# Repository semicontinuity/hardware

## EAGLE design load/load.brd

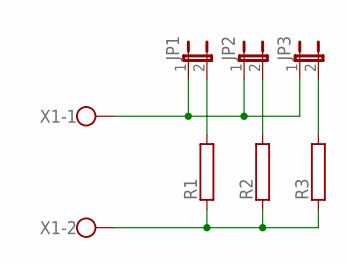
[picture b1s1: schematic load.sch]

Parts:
JP1, JP2, JP3: JP1E; JP1
R1, R2, R3: RRWM8X26; RWM8X26
X1: W237-02P; W237-132

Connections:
GND: R1.1, R2.1, R3.1, X1.2
unnamed: JP1.2, R1.2
unnamed: JP2.2, R2.2
unnamed: JP3.2, R3.2
VCC: JP1.1, JP2.1, JP3.1, X1.1

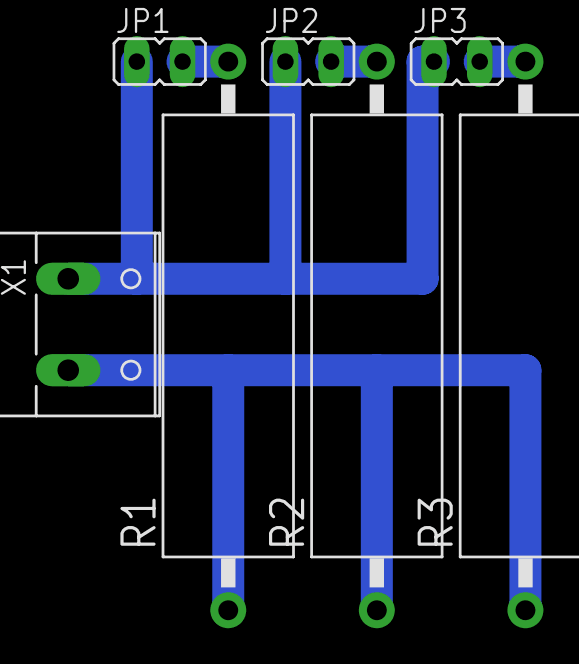
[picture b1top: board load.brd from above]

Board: 2 copper layers, 7 parts (0 on the bottom side), 5 nets.

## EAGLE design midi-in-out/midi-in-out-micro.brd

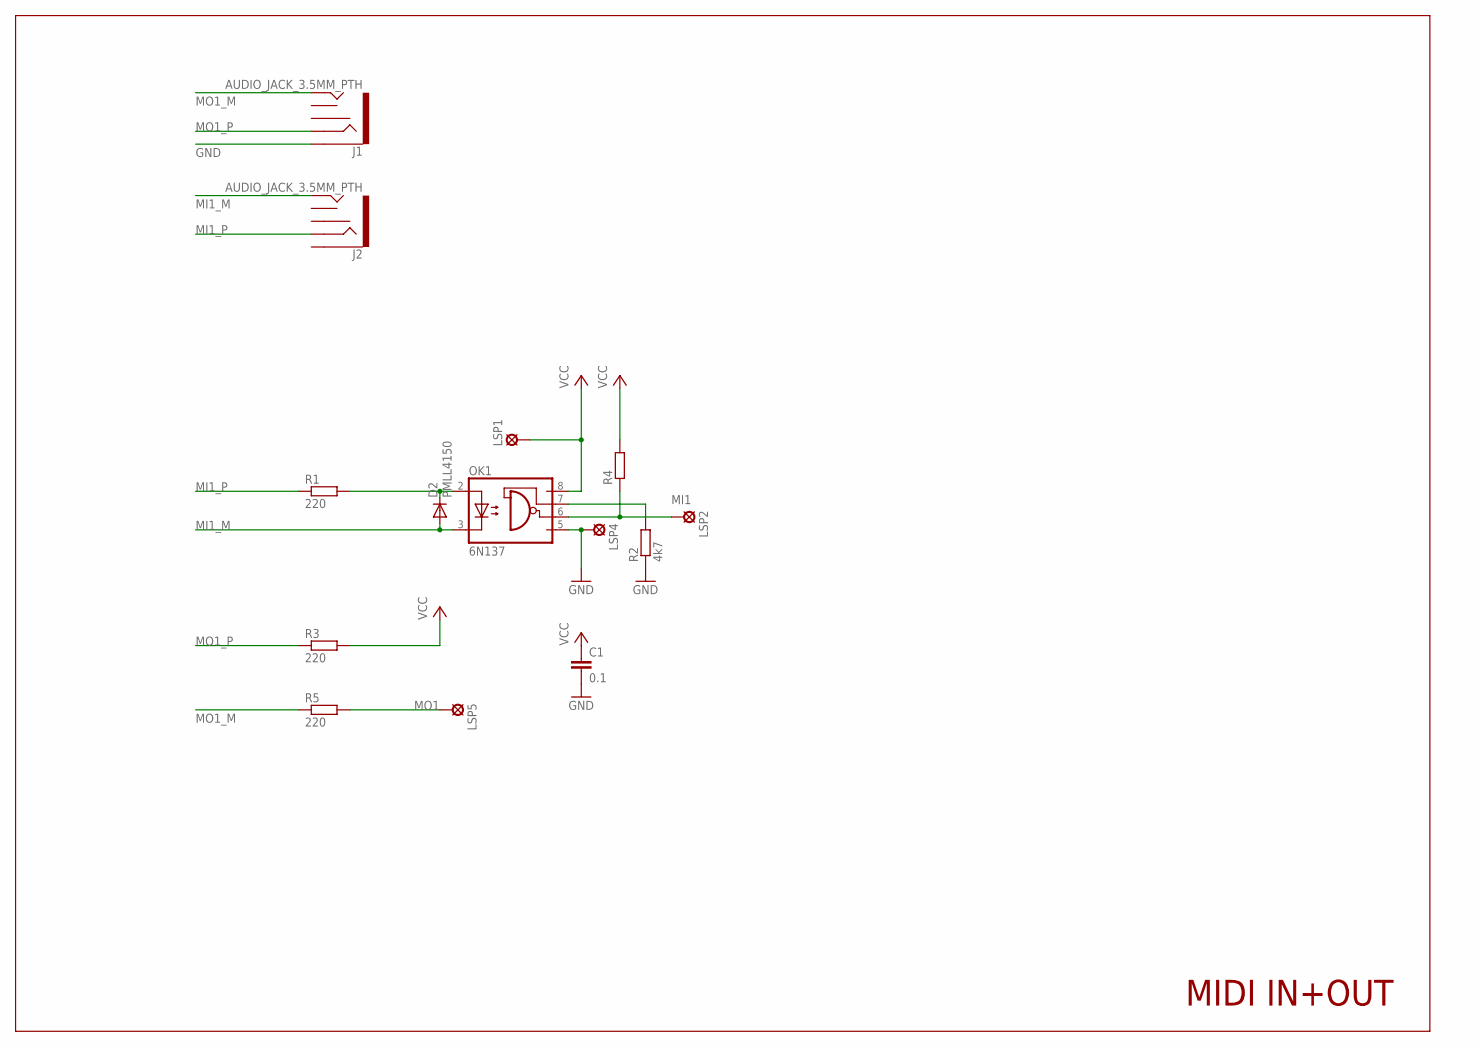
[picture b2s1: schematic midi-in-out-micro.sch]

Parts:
C1: 0.1; C0805
D2: PMLL4150; SOD80C
J1, J2: AUDIO_JACK_3.5MM_PTH; AUDIO-JACK
LSP1, LSP2, LSP4, LSP5: MCS10B
OK1: 6N137; DIL08
R1, R3, R5: 220; R0805
R2: 4k7; R0805
R4: R-EU_0207/5V; 0207/5V

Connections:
GND: C1.2, J1.SLEEVE, LSP4.MP, OK1.5 (GND), R2.1
MI1: LSP2.MP, OK1.6 (VO), R4.1
MI1_M: D2.A, J2.TIP, OK1.3 (C)
MI1_P: J2.RING, R1.1
MO1: LSP5.MP, R5.2
MO1_M: J1.TIP, R5.1
MO1_P: J1.RING, R3.1
unnamed: D2.C, OK1.2 (A), R1.2
unnamed: OK1.7 (VE), R2.2
VCC: C1.1, LSP1.MP, OK1.8 (VCC), R3.2, R4.2

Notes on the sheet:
MIDI IN+OUT

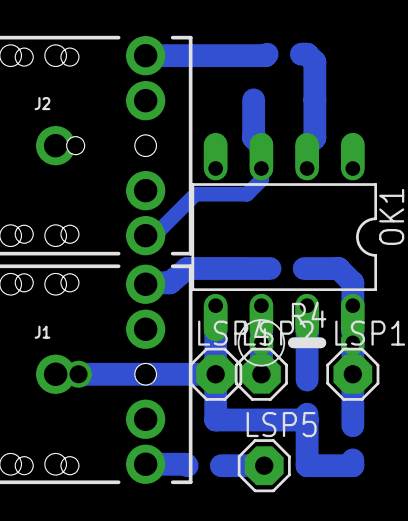
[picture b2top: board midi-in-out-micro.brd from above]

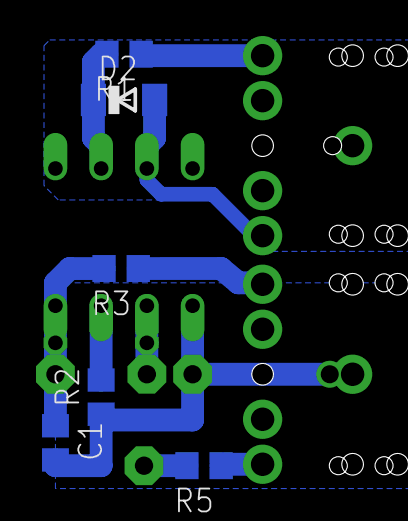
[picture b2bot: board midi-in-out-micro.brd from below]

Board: 2 copper layers, 14 parts (6 on the bottom side), 10 nets.

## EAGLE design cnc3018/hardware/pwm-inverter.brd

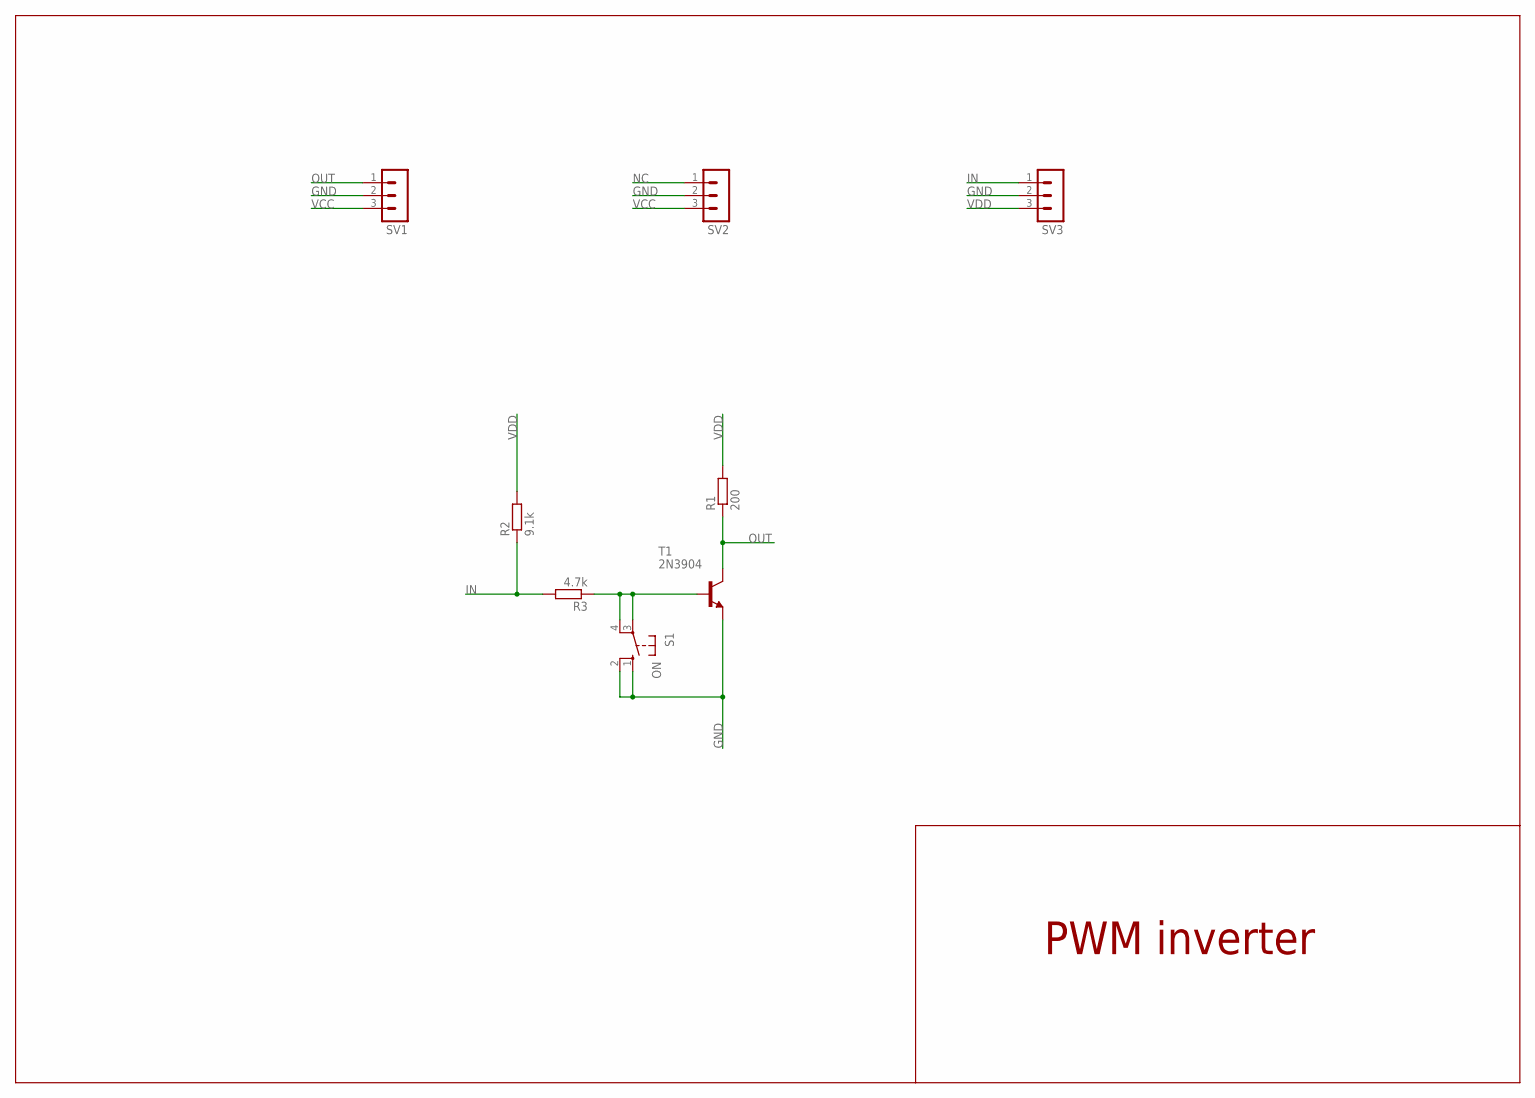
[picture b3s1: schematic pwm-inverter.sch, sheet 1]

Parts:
R1: 200; 0207/10
R2: 9.1k; 0207/10
R3: 4.7k; 0207/10
S1: ON; B3F-10XX
SV1, SV2, SV3: MA03-1
T1: 2N3904; TO92

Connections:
GND: S1.1 (S), S1.2 (S1), SV1.2, SV2.2, SV3.2, T1.3 (E)
IN: R2.1, R3.2, SV3.1
unnamed: R3.1, S1.3, S1.4 (P1), T1.2 (B)
NC: SV2.1
OUT: R1.1, SV1.1, T1.1 (C)
VCC: SV1.3, SV2.3
VDD: R1.2, R2.2, SV3.3

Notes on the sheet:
PWM inverter

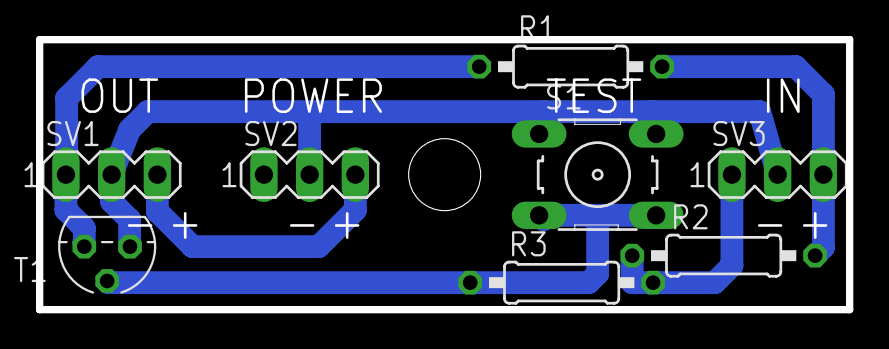
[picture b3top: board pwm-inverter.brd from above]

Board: 2 copper layers, 45.0 x 15.0 mm, 8 parts (0 on the bottom side), 6 nets.

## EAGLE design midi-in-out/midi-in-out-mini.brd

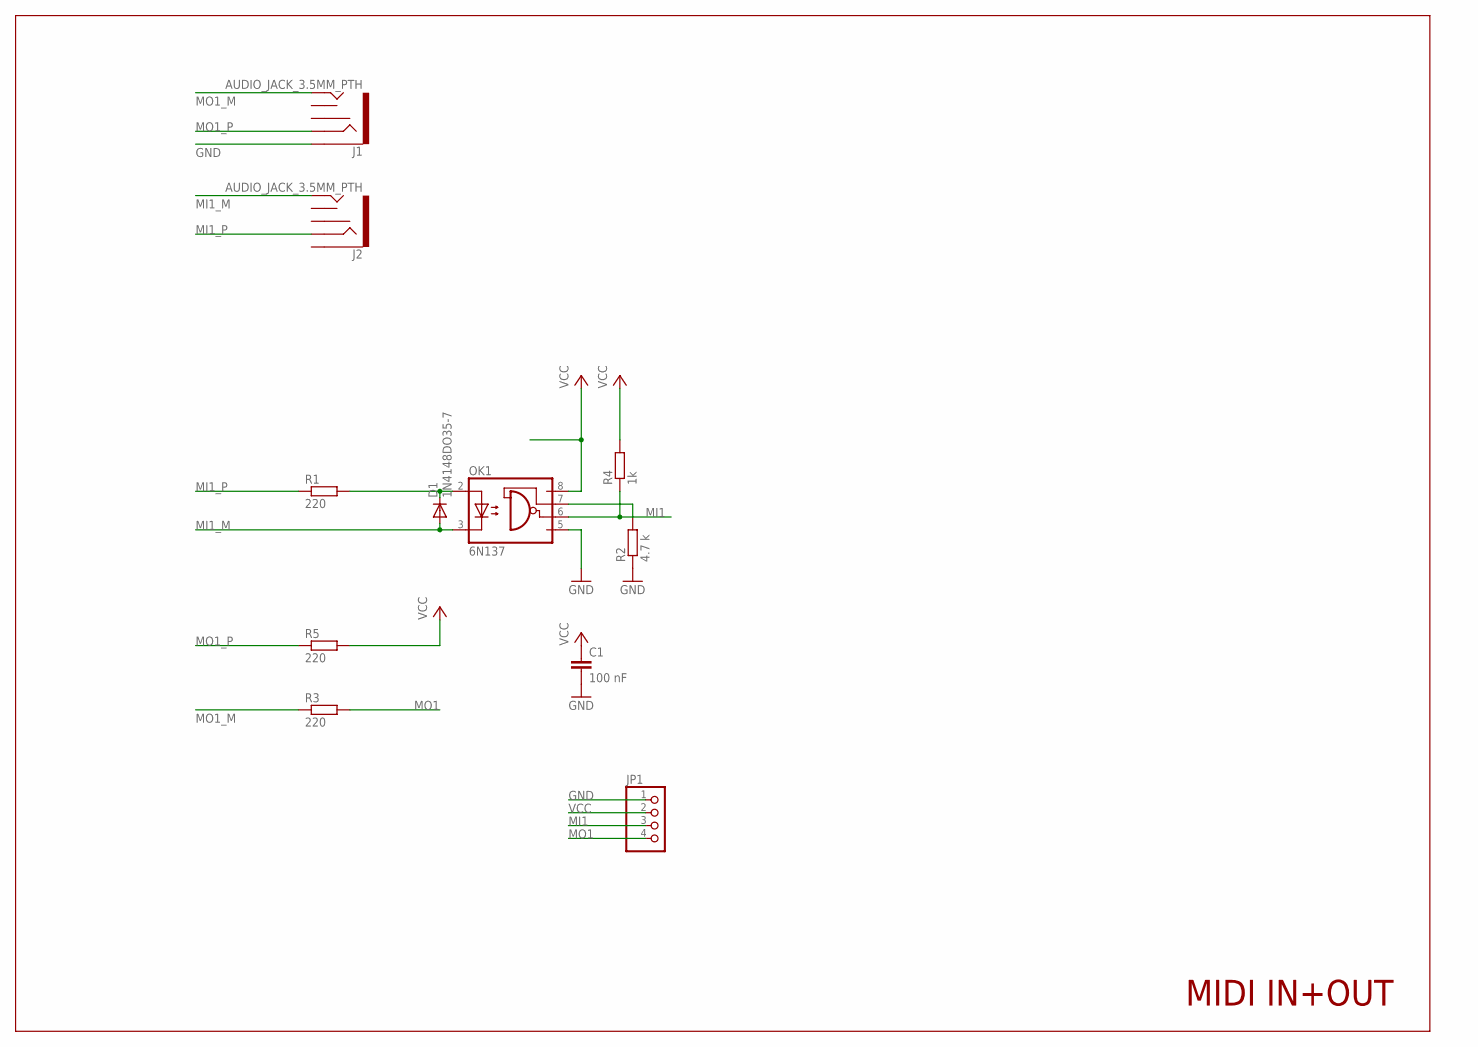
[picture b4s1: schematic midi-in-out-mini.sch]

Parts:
C1: 100 nF; C025-024X044
D1: 1N4148DO35-7; DO35-7
J1, J2: AUDIO_JACK_3.5MM_PTH; AUDIO-JACK
JP1: PINHD-1X4/90; 1X04/90
OK1: 6N137; DIL08
R1, R3, R5: 220; 0204/7
R2: 4.7 k; 0204/7
R4: 1k; 0204/7

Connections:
GND: C1.2, J1.SLEEVE, JP1.1, OK1.5 (GND), R2.1
MI1: JP1.3, OK1.6 (VO), R4.1
MI1_M: D1.A, J2.TIP, OK1.3 (C)
MI1_P: J2.RING, R1.1
MO1: JP1.4, R3.2
MO1_M: J1.TIP, R3.1
MO1_P: J1.RING, R5.1
unnamed: D1.C, OK1.2 (A), R1.2
unnamed: OK1.7 (VE), R2.2
VCC: C1.1, JP1.2, OK1.8 (VCC), R4.2, R5.2

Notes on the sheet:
MIDI IN+OUT

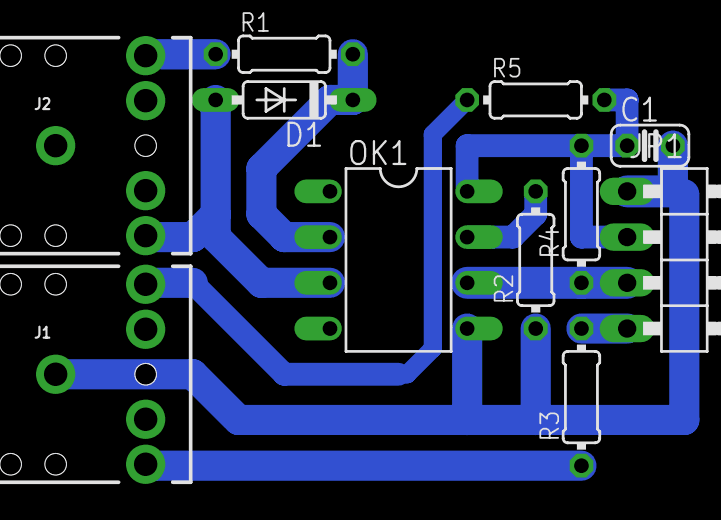
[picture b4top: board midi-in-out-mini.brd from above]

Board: 2 copper layers, 11 parts (0 on the bottom side), 10 nets.

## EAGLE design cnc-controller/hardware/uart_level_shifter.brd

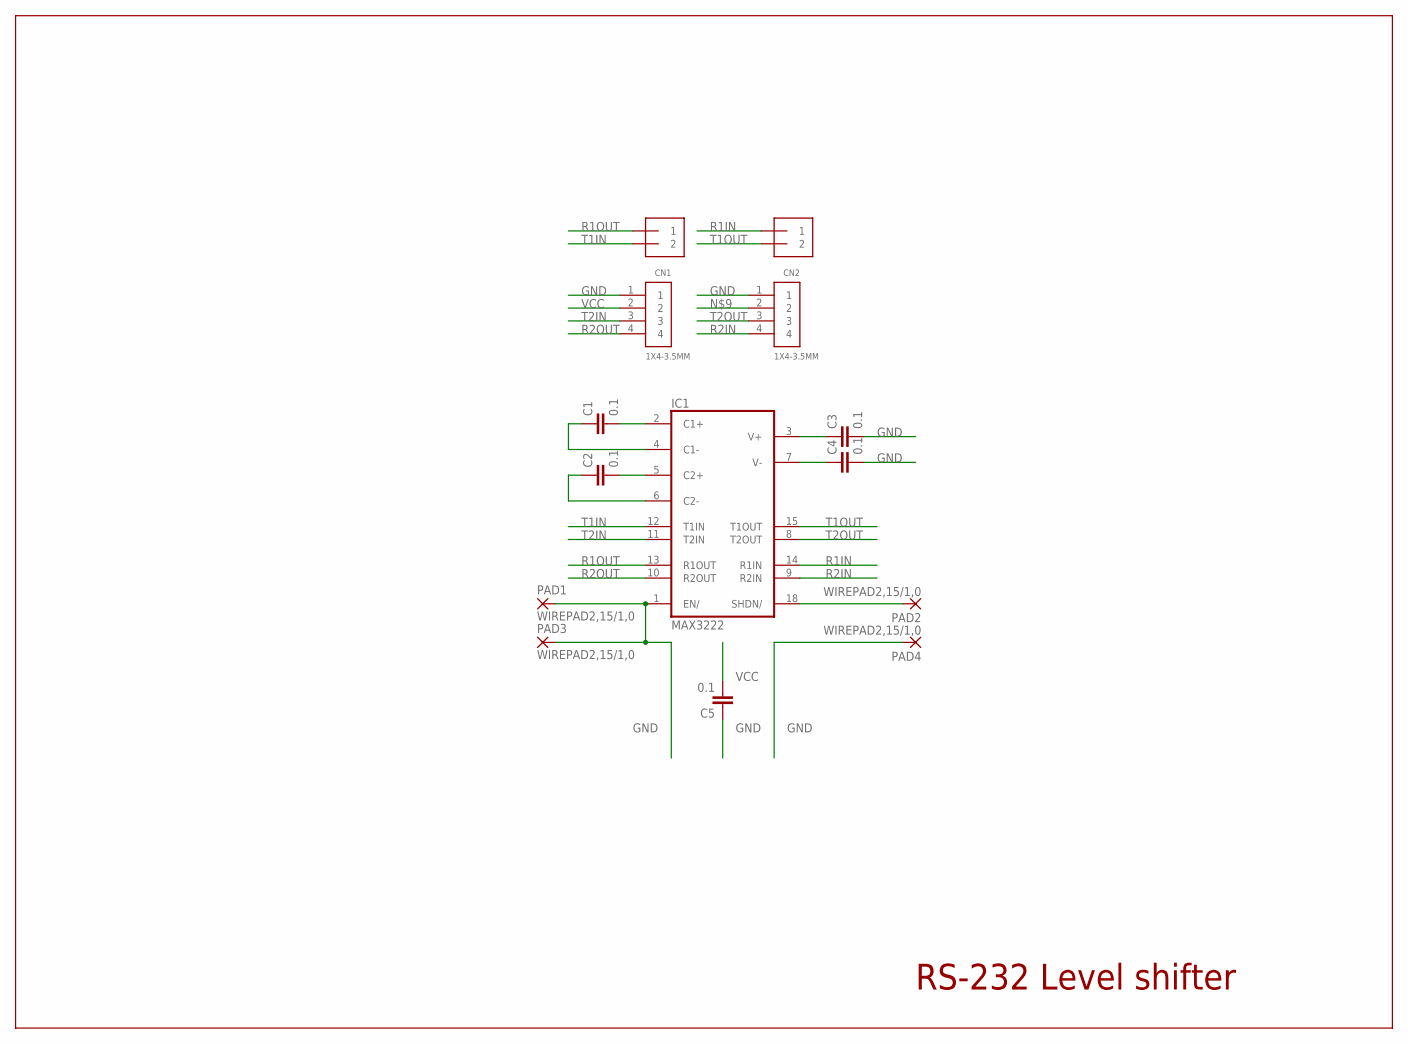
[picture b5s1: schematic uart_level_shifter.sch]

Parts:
C1, C2, C3, C4, C5: 0.1; C0805
CN1, CN2: 1X4-3.5MM; 1X04-3.5MM
IC1: MAX3222; DIL18
J1, J2: 1X2-3.5MM
PAD1, PAD2, PAD3, PAD4: WIREPAD2,15/1,0; 2,15/1,0

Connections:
GND: C3.2, C4.2, C5.1, CN1.1, CN2.1, IC1.1 (EN/), IC1.16 (GND), PAD1.1, PAD3.1, PAD4.1
unnamed: C2.2, IC1.5 (C2+)
unnamed: C2.1, IC1.6 (C2-)
unnamed: C1.1, IC1.4 (C1-)
unnamed: C1.2, IC1.2 (C1+)
unnamed: C3.1, IC1.3 (V+)
unnamed: IC1.18 (SHDN/), PAD2.1
unnamed: C4.1, IC1.7 (V-)
R1IN: IC1.14 (R1IN), J2.1
R1OUT: IC1.13 (R1OUT), J1.1
R2IN: CN2.4, IC1.9 (R2IN)
R2OUT: CN1.4, IC1.10 (R2OUT)
T1IN: IC1.12 (T1IN), J1.2
T1OUT: IC1.15 (T1OUT), J2.2
T2IN: CN1.3, IC1.11 (T2IN)
T2OUT: CN2.3, IC1.8 (T2OUT)
VCC: C5.2, CN1.2, IC1.17 (VCC)

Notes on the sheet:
RS-232 Level shifter

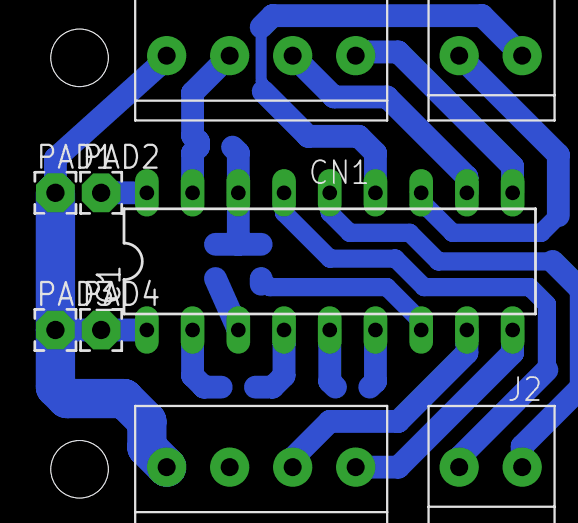
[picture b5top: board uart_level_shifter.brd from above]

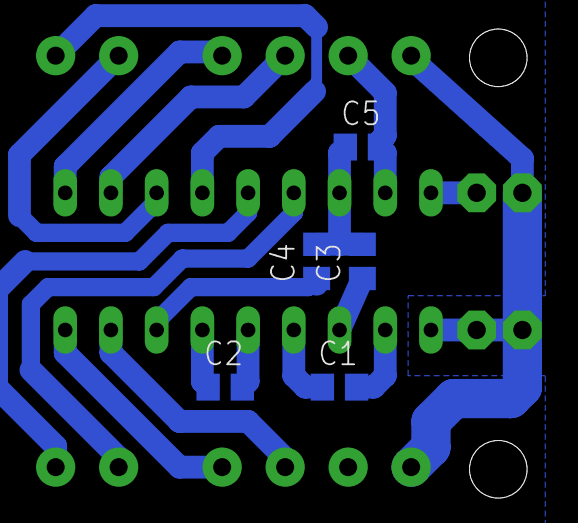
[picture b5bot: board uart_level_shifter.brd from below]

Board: 2 copper layers, 14 parts (5 on the bottom side), 17 nets.

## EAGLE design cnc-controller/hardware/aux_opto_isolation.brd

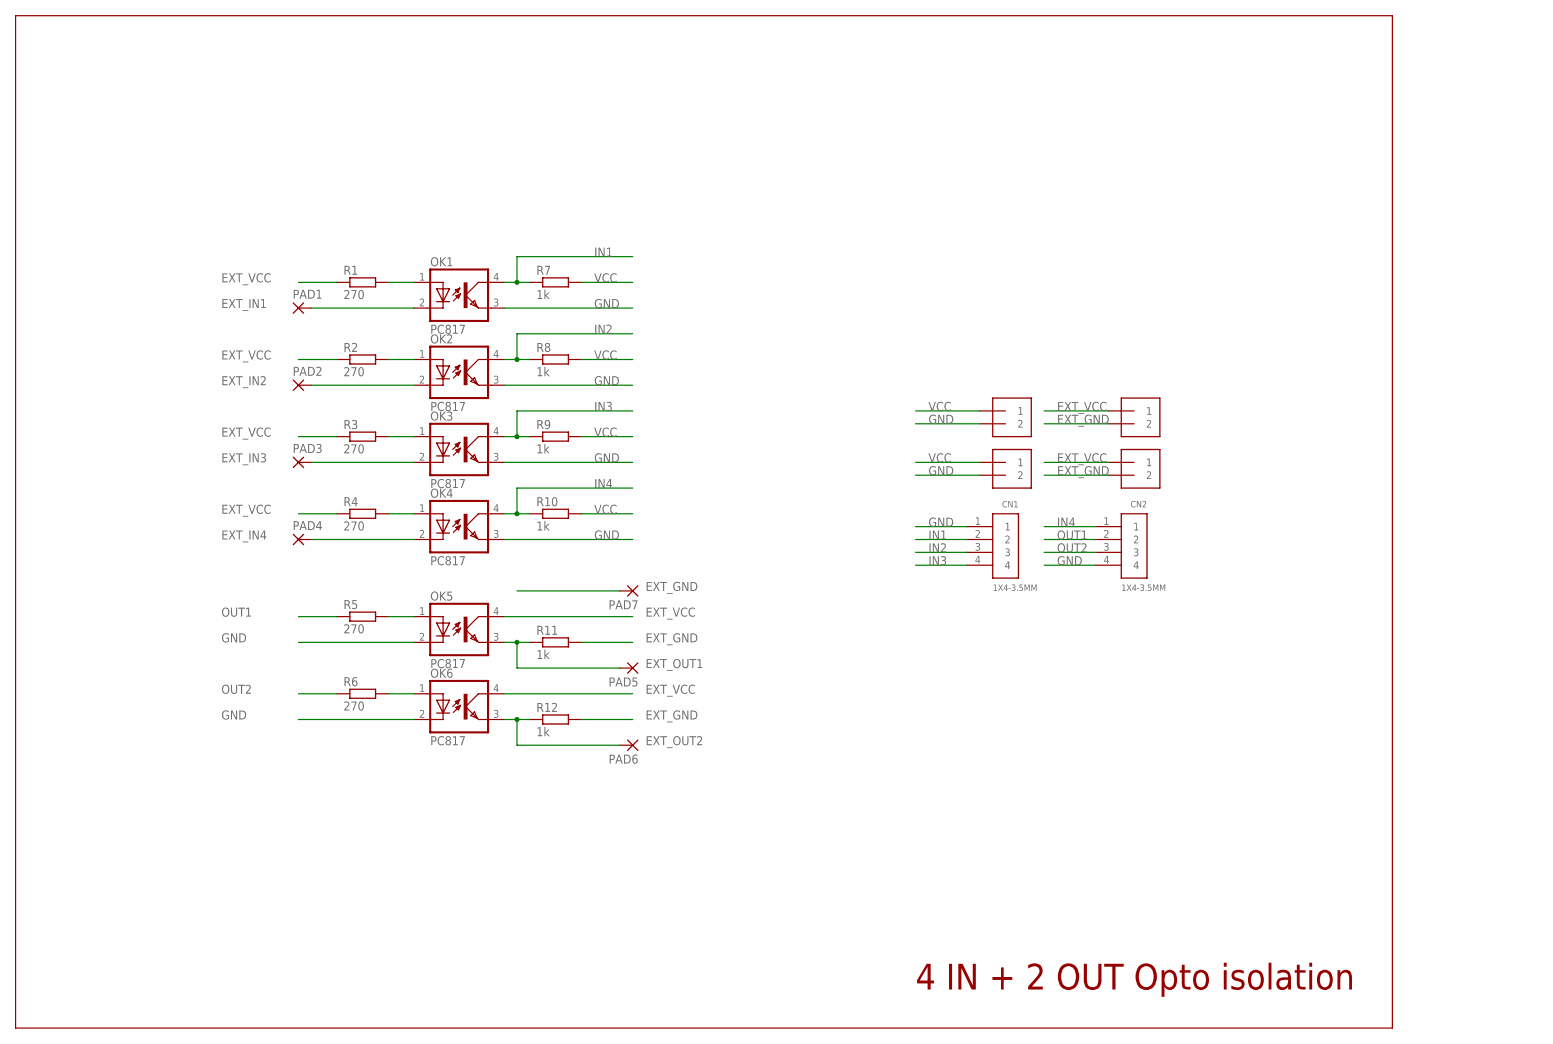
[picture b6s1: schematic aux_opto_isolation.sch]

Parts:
CN1, CN2: 1X4-3.5MM; 1X04-3.5MM
J1, J2, J3, J4: 1X2-3.5MM
OK1, OK2, OK3, OK4, OK5, OK6: PC817; DIL04
PAD1, PAD2, PAD3, PAD4, PAD5, PAD6, PAD7: 2,54/1,0
R1, R2, R3, R4, R5, R6: 270; M0805
R7, R8, R9, R10, R11, R12: 1k; M0805

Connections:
EXT_GND: J2.2, J4.2, PAD7.1, R11.2, R12.2
EXT_IN1: OK1.2 (C), PAD1.1
EXT_IN2: OK2.2 (C), PAD2.1
EXT_IN3: OK3.2 (C), PAD3.1
EXT_IN4: OK4.2 (C), PAD4.1
EXT_OUT1: OK5.3 (EMIT), PAD5.1, R11.1
EXT_OUT2: OK6.3 (EMIT), PAD6.1, R12.1
EXT_VCC: J2.1, J4.1, OK5.4 (COL), OK6.4 (COL), R1.1, R2.1, R3.1, R4.1
GND: CN1.1, CN2.4, J1.2, J3.2, OK1.3 (EMIT), OK2.3 (EMIT), OK3.3 (EMIT), OK4.3 (EMIT), OK5.2 (C), OK6.2 (C)
IN1: CN1.2, OK1.4 (COL), R7.1
IN2: CN1.3, OK2.4 (COL), R8.1
IN3: CN1.4, OK3.4 (COL), R9.1
IN4: CN2.1, OK4.4 (COL), R10.1
unnamed: OK5.1 (A), R5.2
unnamed: OK6.1 (A), R6.2
unnamed: OK2.1 (A), R2.2
unnamed: OK3.1 (A), R3.2
unnamed: OK4.1 (A), R4.2
unnamed: OK1.1 (A), R1.2
OUT1: CN2.2, R5.1
OUT2: CN2.3, R6.1
VCC: J1.1, J3.1, R7.2, R8.2, R9.2, R10.2

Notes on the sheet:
4 IN + 2 OUT Opto isolation

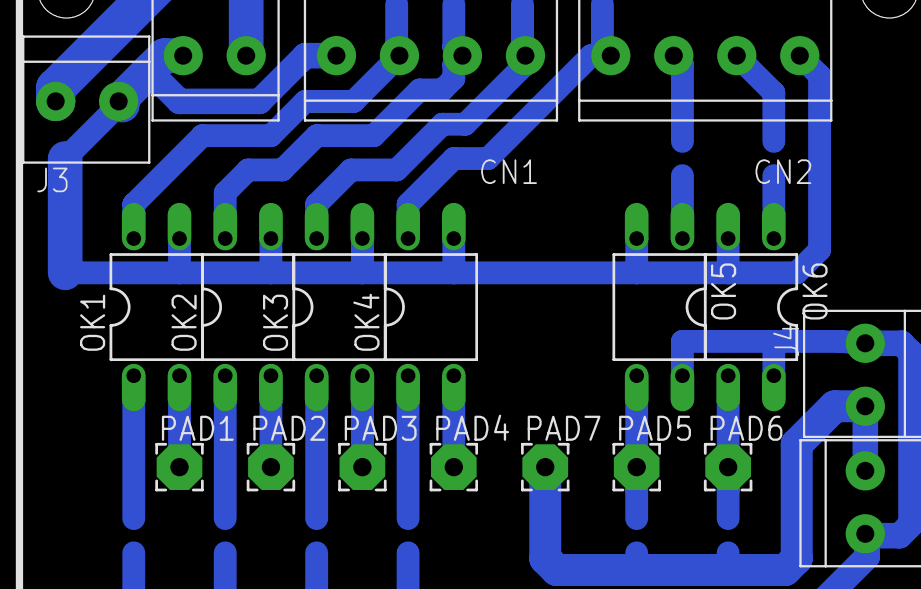
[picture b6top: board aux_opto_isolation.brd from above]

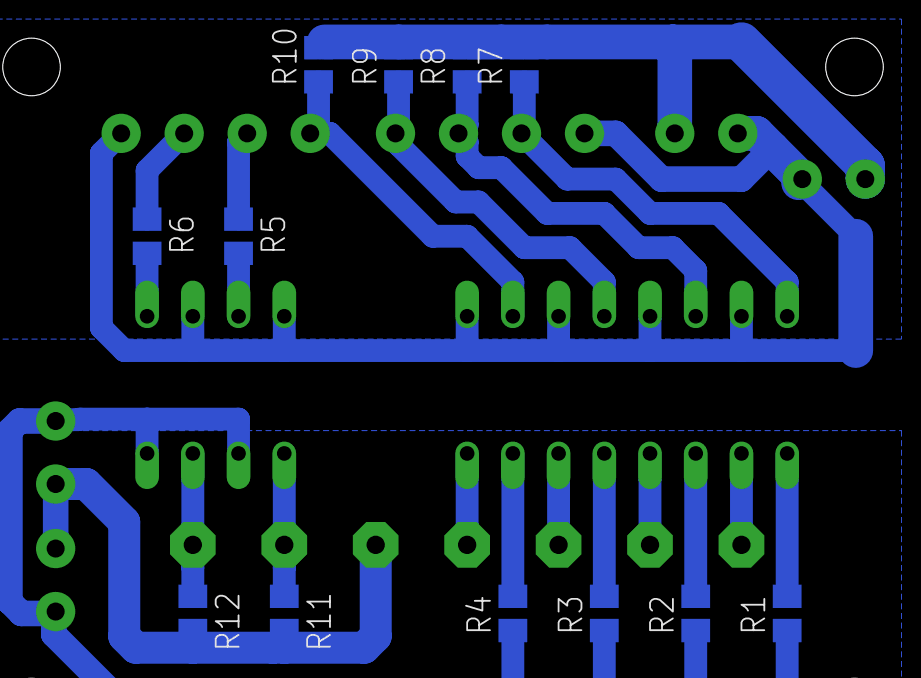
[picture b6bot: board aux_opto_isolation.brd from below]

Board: 2 copper layers, 31 parts (12 on the bottom side), 22 nets.

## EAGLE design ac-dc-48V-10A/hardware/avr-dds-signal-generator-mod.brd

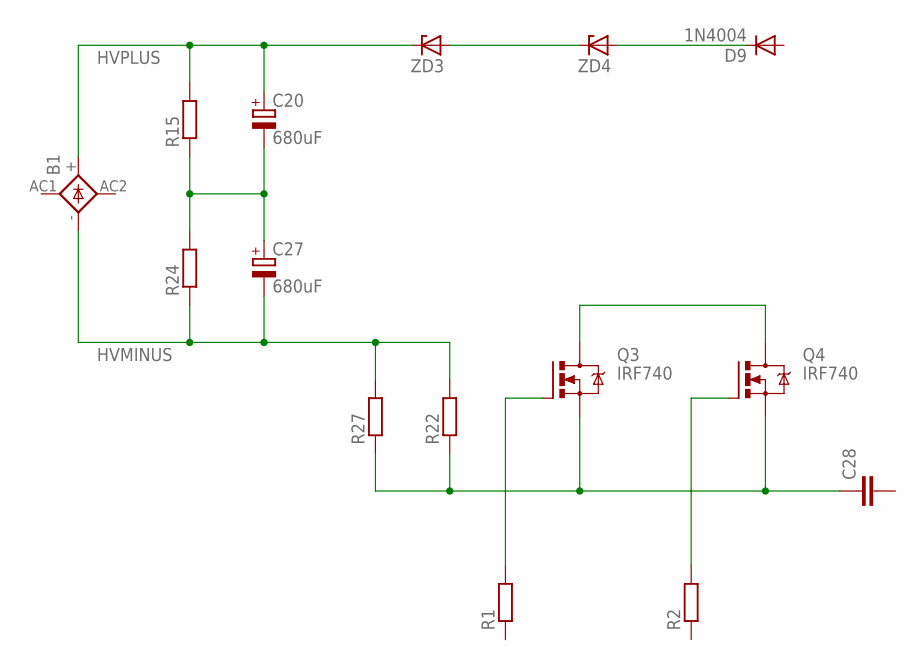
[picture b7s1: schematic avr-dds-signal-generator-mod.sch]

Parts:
B1: KBU
C20, C27: 680uF; EB22,5D
C28: C-EU025-025X050; C025-025X050
D9: 1N4004; DO41-10
Q3, Q4: IRF740; TO220BV
R1, R2, R15, R24: R-EU_0309/12; 0309/12
R22, R27: R-EU_0414/15; 0414/15
ZD3, ZD4: ZENER-DIODEC1702-15; C1702-15

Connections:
HVMINUS: B1.-, C27.-, R22.2, R24.1, R27.2
HVPLUS: B1.+, C20.+, R15.2, ZD3.C
unnamed: ZD3.A, ZD4.C
unnamed: C20.-, C27.+, R15.1, R24.2
unnamed: D9.C, ZD4.A
unnamed: C28.1, Q3.S, Q4.S, R22.1, R27.1
unnamed: Q3.D, Q4.D
unnamed: Q3.G, R1.2
unnamed: Q4.G, R2.2

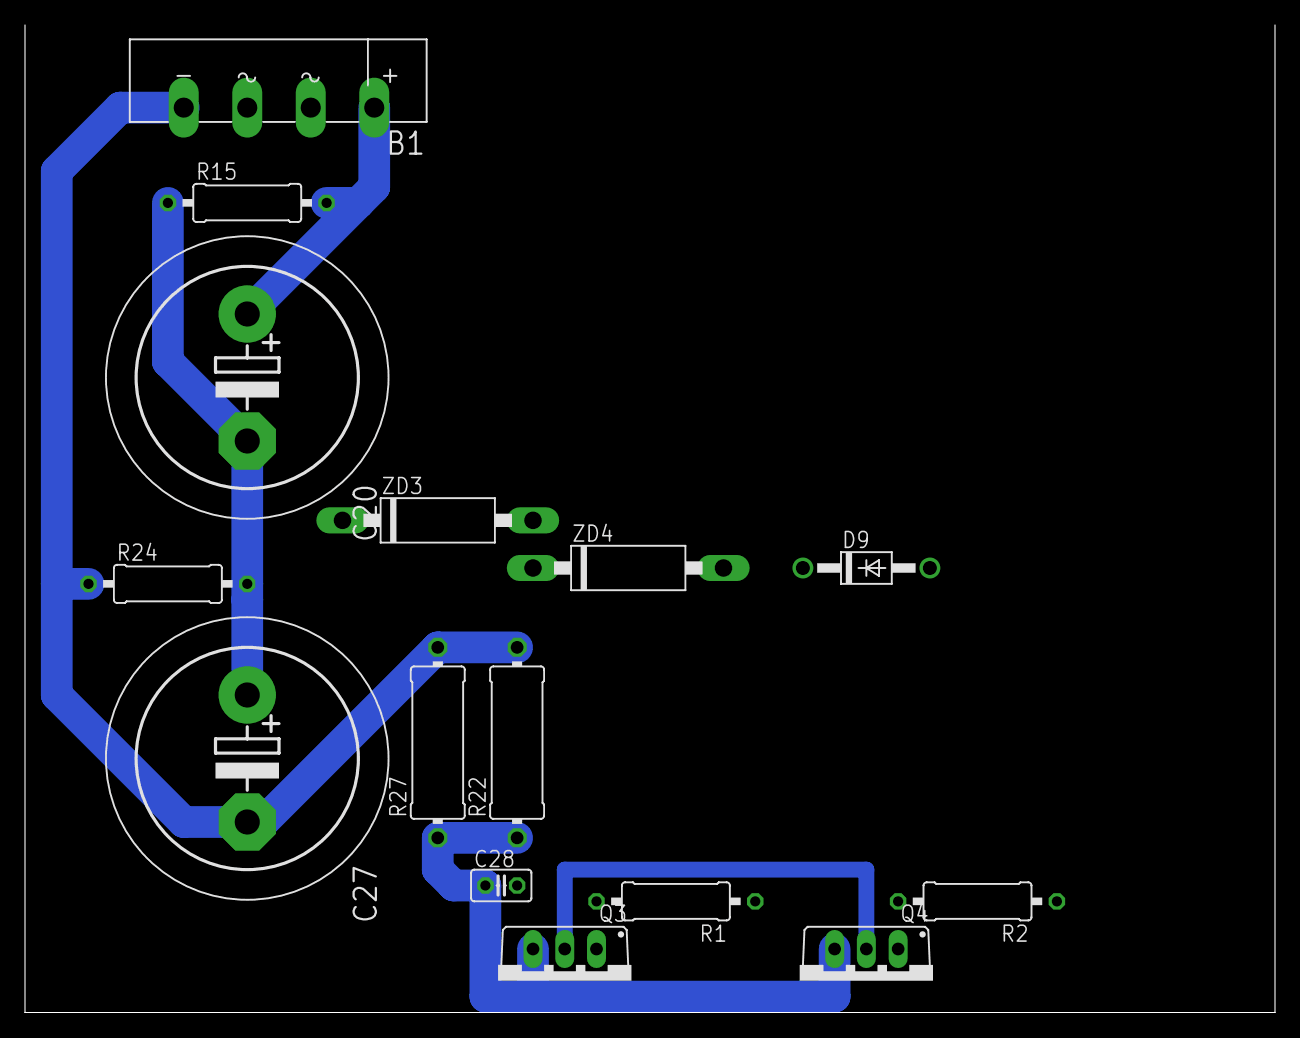
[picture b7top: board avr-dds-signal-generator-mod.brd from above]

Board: 2 copper layers, 100.0 x 79.0 mm, 15 parts (0 on the bottom side), 9 nets.

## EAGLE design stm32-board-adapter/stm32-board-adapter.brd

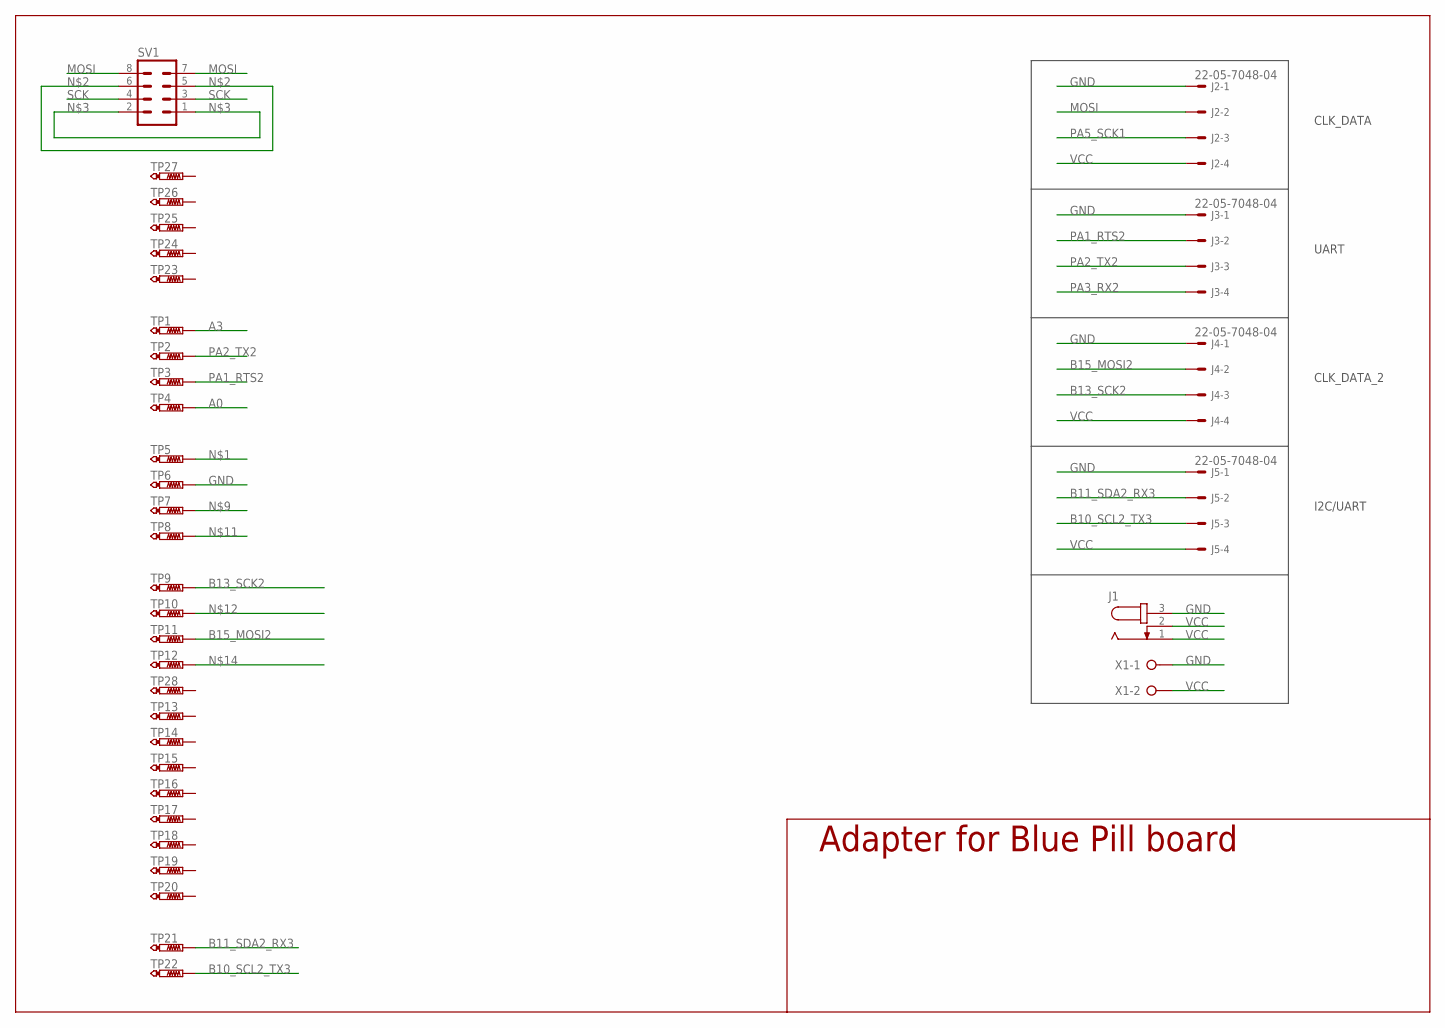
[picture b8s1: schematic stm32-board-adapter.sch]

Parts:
J1: JACK-PLUG1; SPC4078
J2, J3, J4, J5: 22-05-7048-04; 7395-04
SV1: MA04-2
TP1, TP2, TP3, TP4, TP5, TP6, TP7, TP8, TP9, TP10, TP11, TP12, TP13, TP14, TP15, TP16, TP17, TP18, TP19, TP20, TP21, TP22, TP23, TP24, TP25, TP26, TP27, TP28: PTR1PAD1-13; P1-13
X1: W237-02P; W237-132

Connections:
A0: TP4.TP
A3: TP1.TP
B10_SCL2_TX3: J5.3, TP22.TP
B11_SDA2_RX3: J5.2, TP21.TP
B13_SCK2: J4.3, TP9.TP
B15_MOSI2: J4.2, TP11.TP
GND: J1.3, J2.1, J3.1, J4.1, J5.1, TP6.TP, X1.1
MOSI: J2.2, SV1.7, SV1.8
unnamed: SV1.5, SV1.6
unnamed: SV1.1, SV1.2
PA1_RTS2: J3.2, TP3.TP
PA2_TX2: J3.3, TP2.TP
PA3_RX2: J3.4
PA5_SCK1: J2.3
SCK: SV1.3, SV1.4
VCC: J1.1, J1.2, J2.4, J4.4, J5.4, X1.2

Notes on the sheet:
Adapter for Blue Pill board
I2C/UART
CLK_DATA
UART
CLK_DATA_2

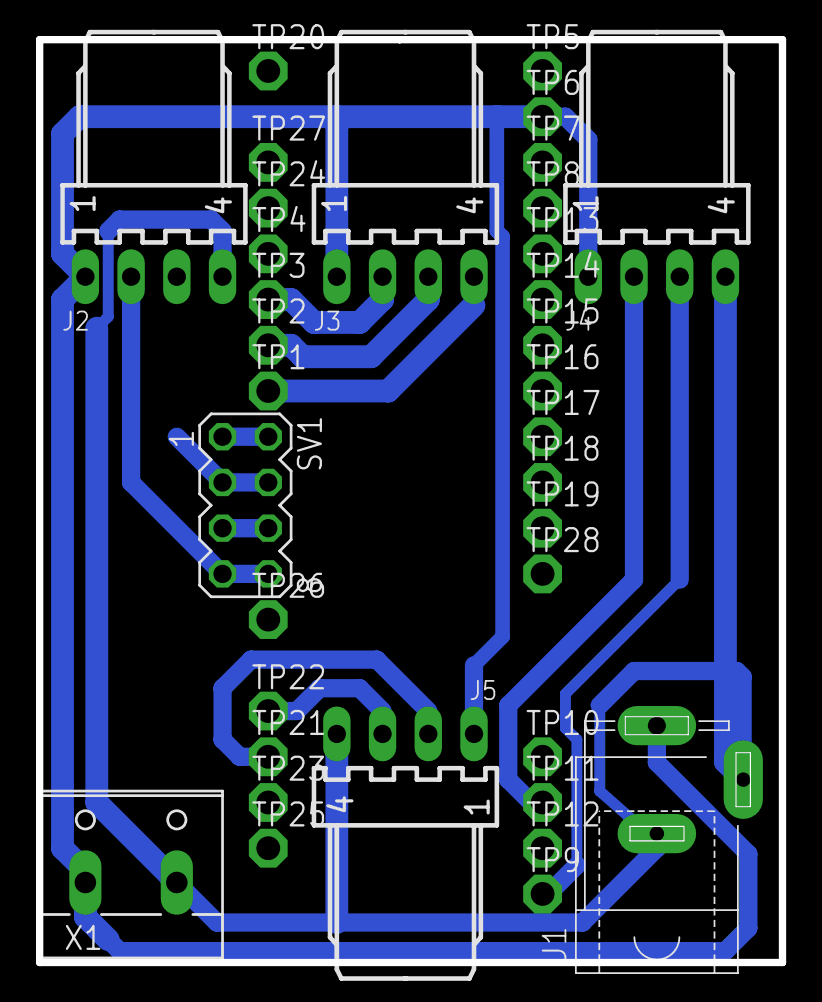
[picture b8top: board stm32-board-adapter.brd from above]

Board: 2 copper layers, 41.3 x 51.3 mm, 35 parts (0 on the bottom side), 12 nets.

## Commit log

2012-07-04 added boards
2012-12-12 added segment_display_2x_static
2013-03-20 added rpi-can-rs485 board
2013-08-28 interim drop
2015-12-24 avr-fusebit-doctor-enhanced
2016-06-14 added stm32-board-adapter
2018-09-06 added rockchip-mics
2019-01-28 added avr-isp-adapter
2019-01-28 added breakout-4x-step-down
2019-01-28 added rpi-display-5110
2019-01-28 added esp8266-adapter
2019-01-28 added my-microchip-pot.lbr
2019-01-28 misc changes
2019-01-28 added tact-switches
2019-01-28 added nas-adapter-board
2019-03-15 eagle-libraries
2019-04-11 midi-in-out: initial schematics and placement
2019-06-03 cnc-spindle-driver
2019-06-19 added avr-fusebit-doctor-adapter-tqfp32
2019-06-19 midi-in-out edits
2019-07-19 case-bottom.scad
2019-07-22 added scad files
2019-07-30 cnc3018: added buttons board
2019-08-01 cnc3018: added arduino shield
2019-08-01 cnc3018: interim drop
2019-08-02 cnc3018 += spindle drivers
2019-08-08 added uart-opto-isolation
2019-09-09 cnc3018: changed buttons board + case
2019-09-09 cnc3018: plates g-code
2019-09-10 cnc3018: fill_rect g-code
2019-09-10 cnc3018: case for opto-isolation board
2019-09-10 cnc3018: fixed cases
2019-11-10 gcode.py: use class
2020-01-10 stm32-board-adapter enhancements
2020-03-04 cnc3018 updates
2020-03-04 added ac-dc-48V-10A
2020-04-14 cnc-controller hardware files
2020-05-25 cnc3018: case holes, front panel
2020-07-01 gcode.py enhancements
2020-08-01 cnc-controller mechanical
2020-10-06 added midi-in-out-mini
2020-12-22 added zebra labels
2020-12-22 cnc3018 update
2021-03-05 cnc-controller labels
2021-06-28 load board
2022-05-04 breakout-i2c-24c02
2022-05-06 breakout-ps2
2023-05-12 plastron plate
2023-05-14 triac-board
2023-05-30 plastron stub
2023-06-24 triac-board-r-top
2023-07-28 button-panel.kicad_pro
2023-07-29 triac-board-front
2024-01-22 far-servo-adapter initial commit
2024-01-23 far-servo-adapter += terminals
2024-03-28 din-3u-button-panel stub
2024-04-12 din-3u-button-panel: update
2024-04-13 din-3u-button-panel-top
2024-04-14 din-3u-button-panel
2024-04-14 button-panel
2024-05-13 wall_outlets_template
2025-04-20 led-panel.kicad
2025-11-20 toggle-switch-panel
2025-11-22 toggle-switch-panel-5x

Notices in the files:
parts and their libraries:
SparkFun-Connectors: Licensing: Creative Commons ShareAlike 4.0 International - https://creativecommons.org/licenses/by-sa/4.0
